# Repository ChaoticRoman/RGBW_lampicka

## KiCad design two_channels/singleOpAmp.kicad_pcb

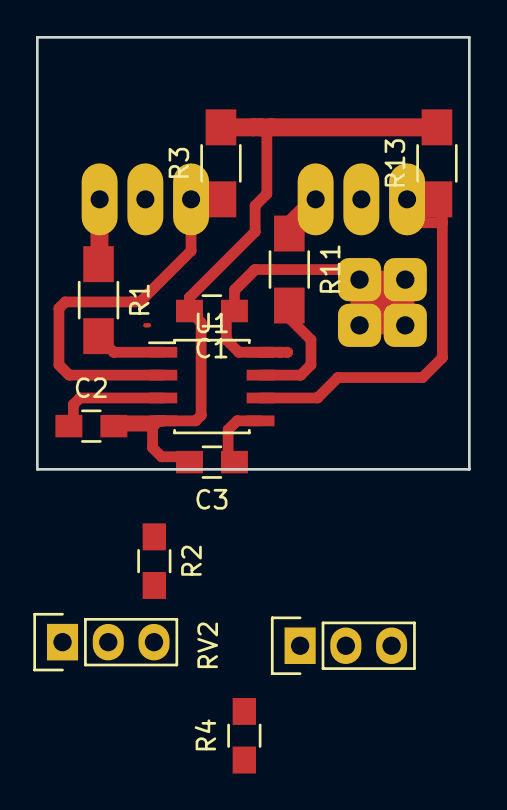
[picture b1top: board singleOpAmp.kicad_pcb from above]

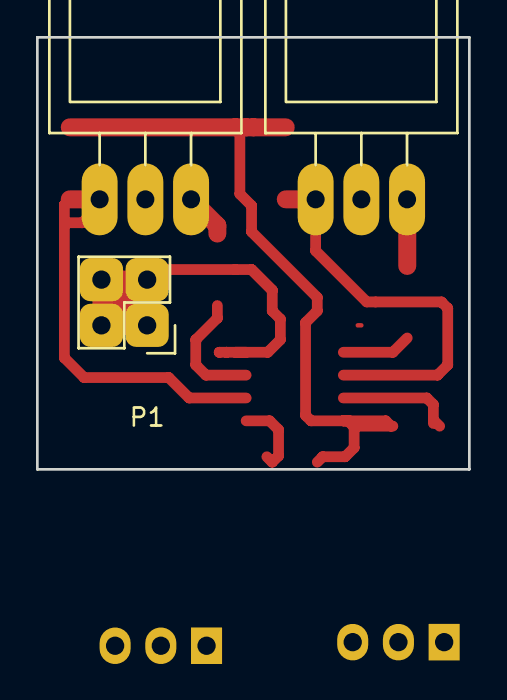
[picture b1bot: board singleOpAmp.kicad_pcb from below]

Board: 2 copper layers, 24.0 x 24.0 mm, 15 parts (3 on the bottom side), 12 nets.

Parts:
C1, C2, C3: 100n; C_0805_HandSoldering
P1: CONN_02X02; Pin_Header_Straight_2x02
Q1, Q2: TIP122; TO-220_Neutral123_Horizontal_Reverse
R1, R11: 8k2; R_1206_HandSoldering
R2, R4: 33k; R_0805_HandSoldering
R3, R13: 1R; R_1206_HandSoldering
RV1, RV2: 5k; Pin_Header_Straight_1x03
U1: LM358N; SOIC-8_3.9x4.9mm_Pitch1.27mm

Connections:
/VCC: C1.1, P1.1, P1.2, P1.3, P1.4, U1.8
GND: C1.2, C2.2, C3.2, R3.2, R13.2, RV1.1, RV2.1, U1.4
unnamed: C2.1, RV1.2, U1.3
unnamed: C3.1, RV2.2, U1.5
unnamed: Q1.1, R11.1
unnamed: Q1.3, R13.1, U1.6
unnamed: Q2.1, R1.1
unnamed: Q2.3, R3.1, U1.2
unnamed: R1.2, U1.1
unnamed: R2.2, RV1.3
unnamed: R4.2, RV2.3
unnamed: R11.2, U1.7

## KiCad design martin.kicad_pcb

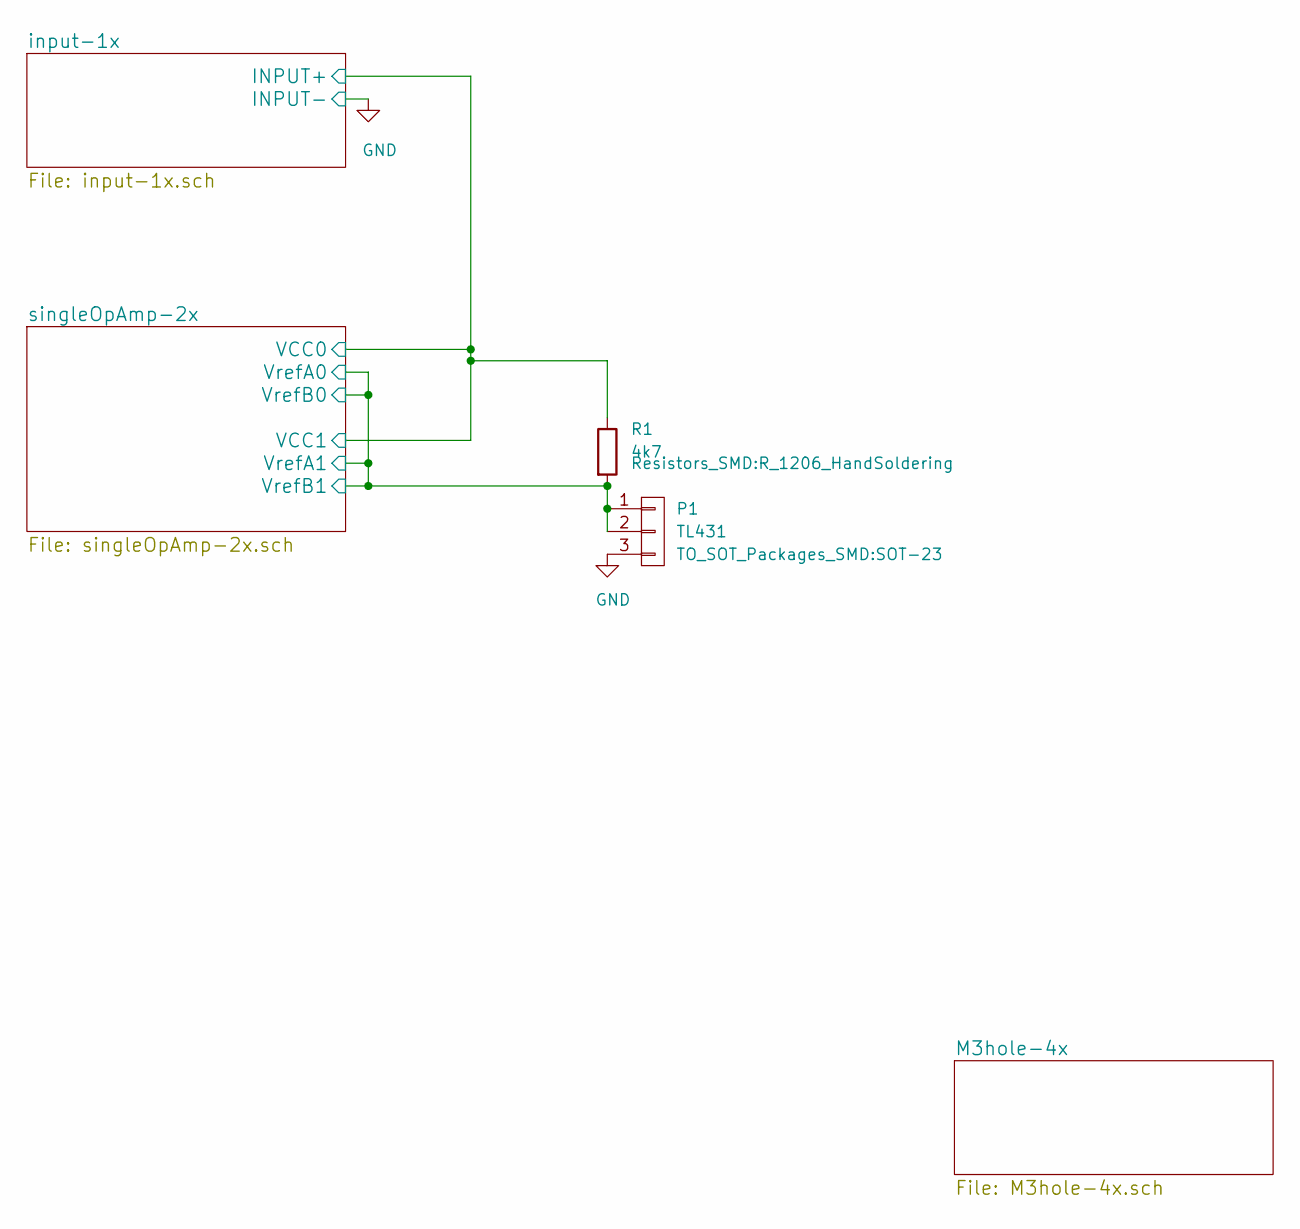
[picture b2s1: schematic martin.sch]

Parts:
P1: TL431; SOT-23
R1: 4k7; R_1206_HandSoldering

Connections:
/input-1x/INPUT+: R1.1; also elsewhere on the board
/singleOpAmp-2x/VrefA0: P1.1, P1.2, R1.2; also elsewhere on the board
GND: P1.3; also elsewhere on the board

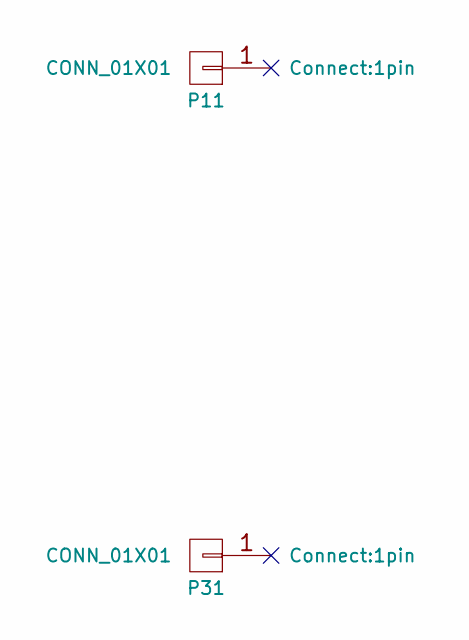
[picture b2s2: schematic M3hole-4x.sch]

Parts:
P11, P31: CONN_01X01; 1pin

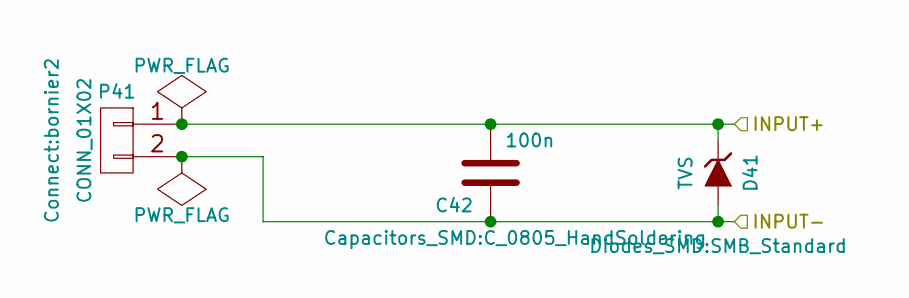
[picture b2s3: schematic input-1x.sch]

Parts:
C42: 100n; C_0805_HandSoldering
D41: TVS; SMB_Standard
P41: CONN_01X02; bornier2

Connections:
/input-1x/INPUT+: C42.2, D41.1 (K), P41.1; also elsewhere on the board
GND: C42.1, D41.2 (A), P41.2; also elsewhere on the board

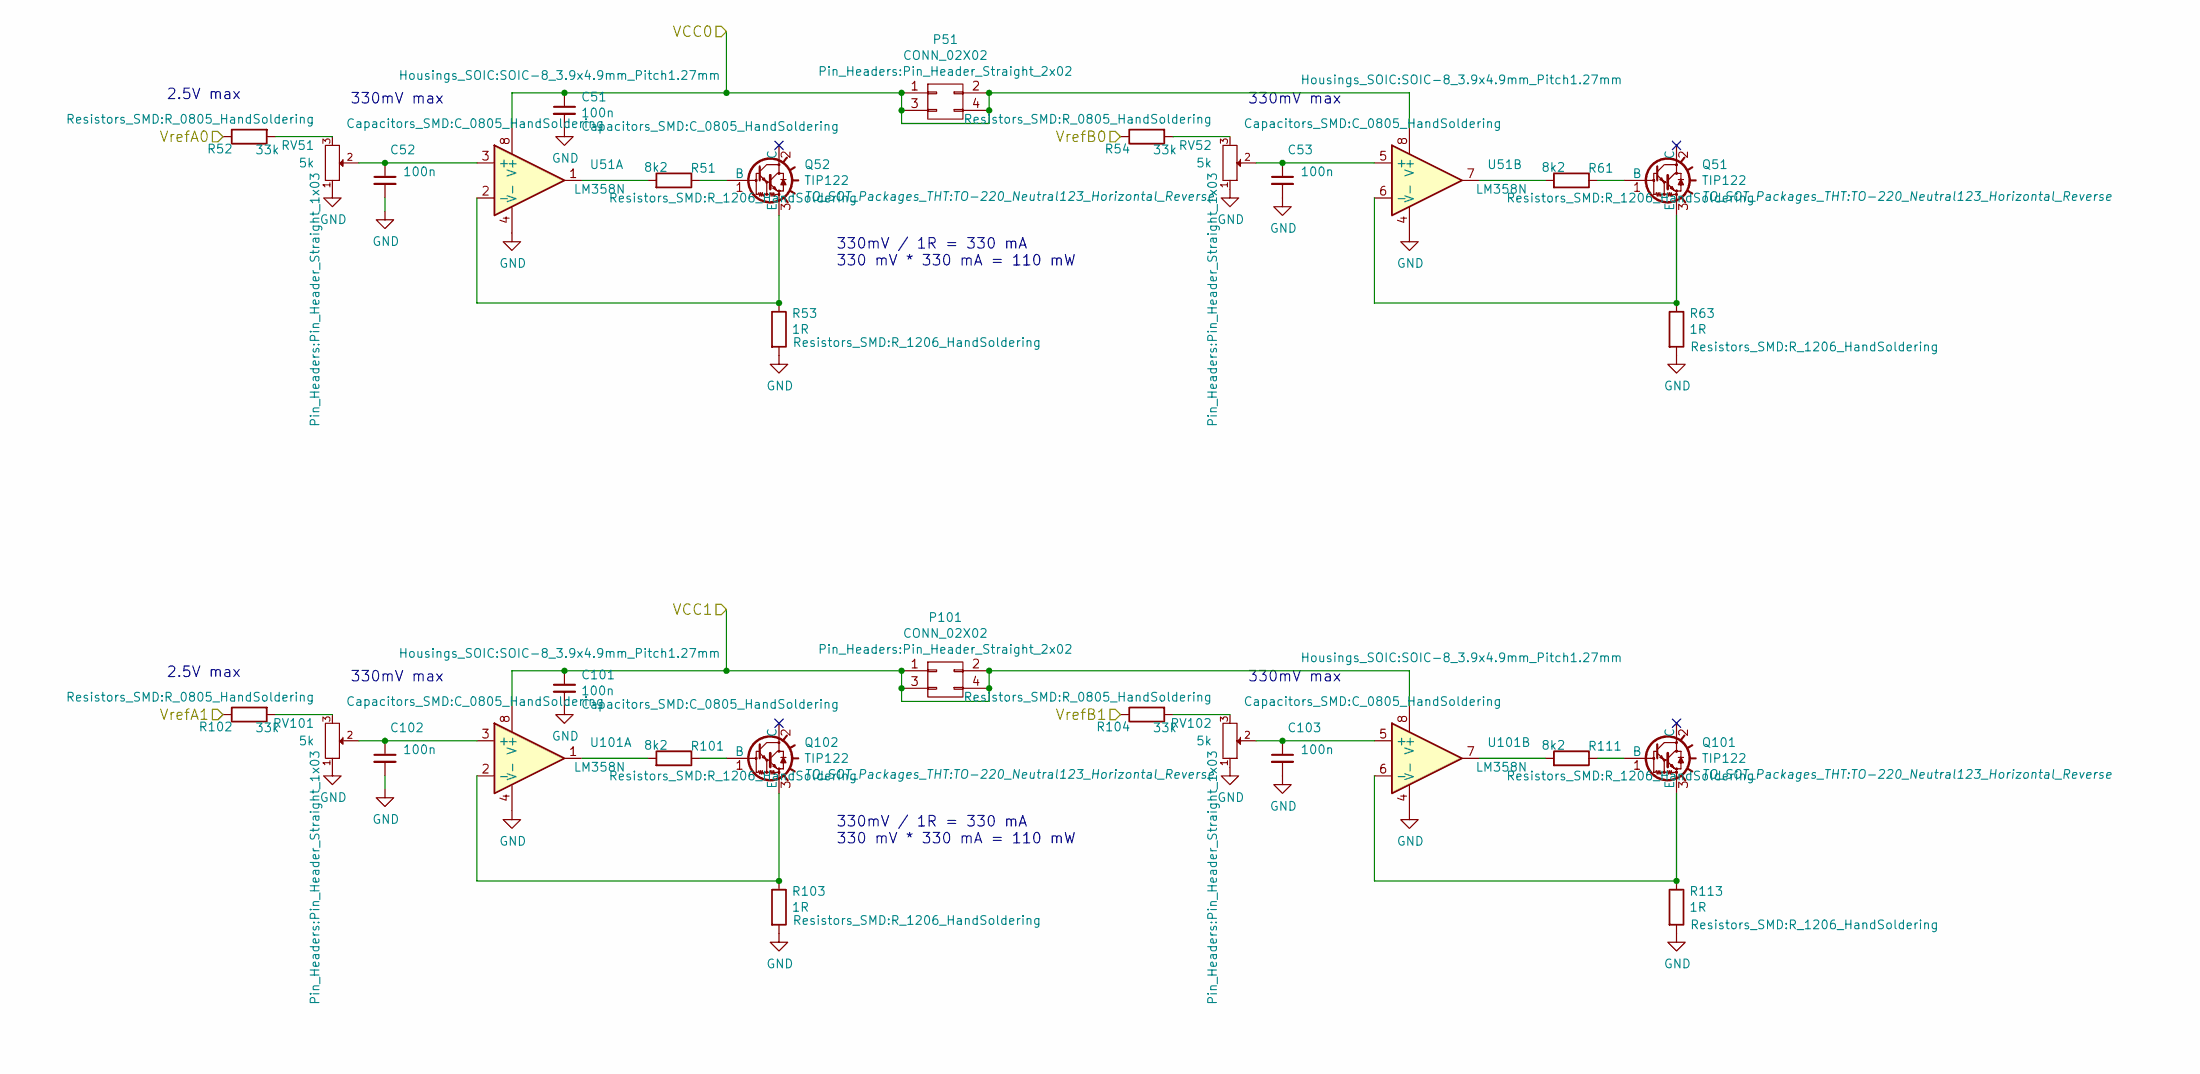
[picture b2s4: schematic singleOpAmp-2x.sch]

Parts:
C51, C52, C53, C101, C102, C103: 100n; C_0805_HandSoldering
P51, P101: CONN_02X02; Pin_Header_Straight_2x02
Q51, Q52, Q101, Q102: TIP122; TO-220_Neutral123_Horizontal_Reverse
R51, R61, R101, R111: 8k2; R_1206_HandSoldering
R52, R54, R102, R104: 33k; R_0805_HandSoldering
R53, R63, R103, R113: 1R; R_1206_HandSoldering
RV51, RV52, RV101, RV102: 5k; Pin_Header_Straight_1x03
U51, U101: LM358N; SOIC-8_3.9x4.9mm_Pitch1.27mm

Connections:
/input-1x/INPUT+: C51.1, C101.1, P51.1, P51.2, P51.3, P51.4, P101.1, P101.2, P101.3, P101.4, U51.8 (V+), U101.8 (V+); also elsewhere on the board
/singleOpAmp-2x/VrefA0: R52.1, R54.1, R102.1, R104.1; also elsewhere on the board
GND: C51.2, C52.2, C53.2, C101.2, C102.2, C103.2, R53.2, R63.2, R103.2, R113.2, RV51.1, RV52.1, RV101.1, RV102.1, U51.4 (V-), U101.4 (V-); also elsewhere on the board
unnamed: C52.1, RV51.2, U51.3 (+)
unnamed: C53.1, RV52.2, U51.5 (+)
unnamed: C102.1, RV101.2, U101.3 (+)
unnamed: C103.1, RV102.2, U101.5 (+)
unnamed: Q51.1 (B), R61.1
unnamed: Q51.3 (E), R63.1, U51.6 (-)
unnamed: Q52.1 (B), R51.1
unnamed: Q52.3 (E), R53.1, U51.2 (-)
unnamed: Q101.1 (B), R111.1
unnamed: Q101.3 (E), R113.1, U101.6 (-)
unnamed: Q102.1 (B), R101.1
unnamed: Q102.3 (E), R103.1, U101.2 (-)
unnamed: R51.2, U51.1
unnamed: R52.2, RV51.3
unnamed: R54.2, RV52.3
unnamed: R61.2, U51.7
unnamed: R101.2, U101.1
unnamed: R102.2, RV101.3
unnamed: R104.2, RV102.3
unnamed: R111.2, U101.7

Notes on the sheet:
330mV max
2.5V max
330mV / 1R = 330 mA 330 mV * 330 mA = 110 mW

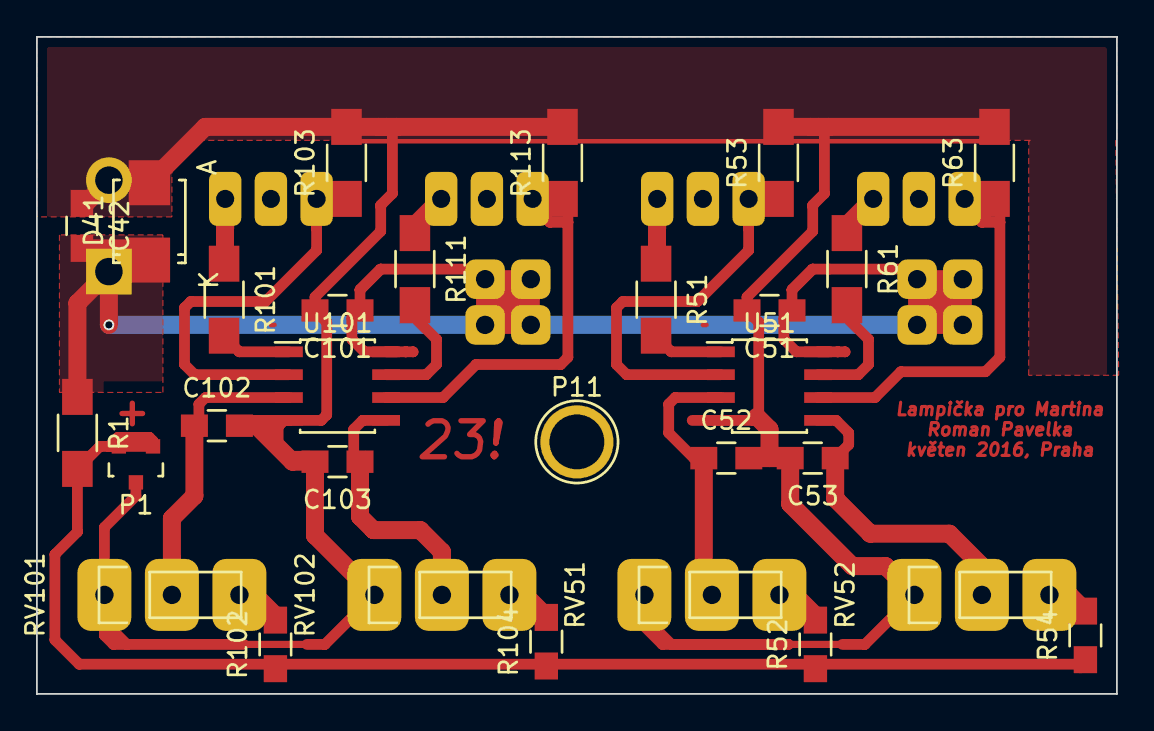
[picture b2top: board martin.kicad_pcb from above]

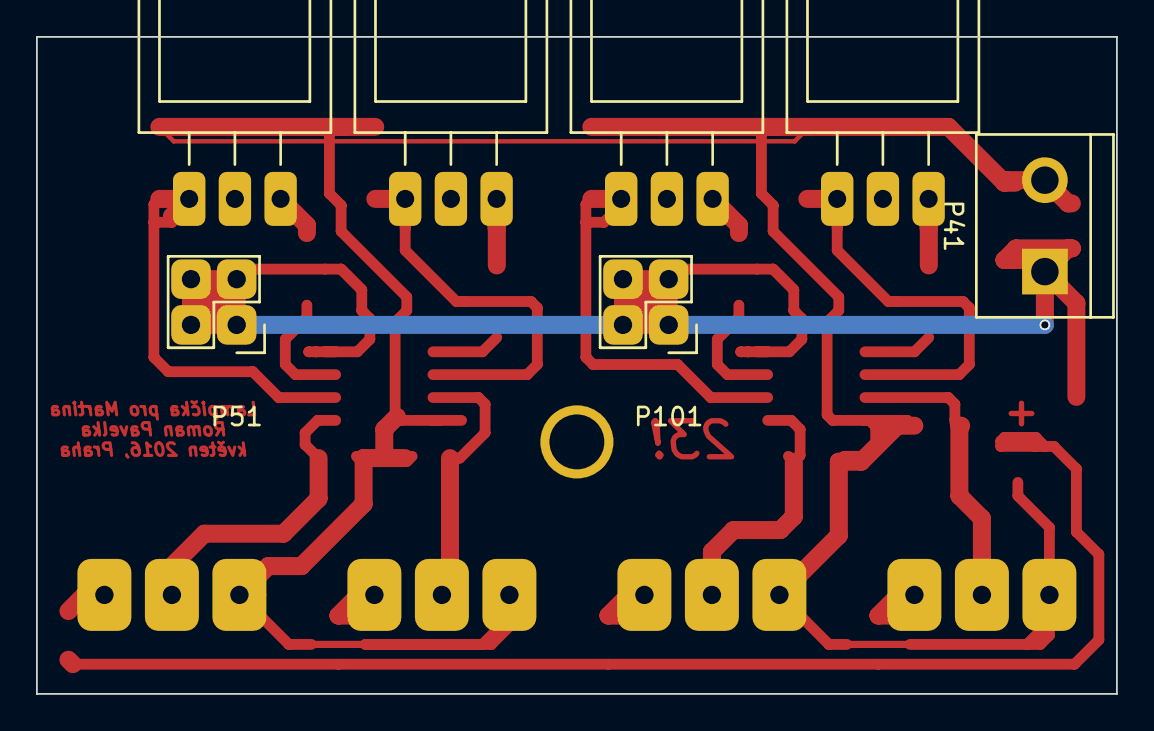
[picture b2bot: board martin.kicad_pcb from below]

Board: 2 copper layers, 60.0 x 36.5 mm, 36 parts (7 on the bottom side), 23 nets.
